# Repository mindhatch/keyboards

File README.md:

# keyboards!
<ul>
  <li>30-34 keys</li>
  <li>choc-spaced</li>
  <li>bluetooth-only</li>
  <li>1.5u thumb keys</li>
  <li>column staggered</li>
  <li>splayed ring and pinky columns</li>
  <li>mcu footprint fits spring-loaded pin headers</li>
</ul>

<h1>ルナ (luna)</h1>
<ul>
  <li>30 keys</li>
  <li>5&deg; splay on ring column</li>
  <li>12.5&deg; splay on pinky column</li>
  <li>switches can be soldered or used with hotswap sockets</li>
  <li>firmware can be found <a href="https://github.com/mindhatch/zmk-config-luna" alt="luna firmware">here</a></li>
</ul>
<br/><br/>

<br/><br/>

<h1>美奈子 (minako)</h1>
<ul>
  <li>32 keys</li>
  <li>5&deg; splay on ring column</li>
  <li>15&deg; splay on pinky column</li>
  <li>switches are solder-only</li>
  <li>firmware can be found <a href="https://github.com/mindhatch/zmk-config-minako" alt="minako firmware">here</a></li>
</ul>
<br/><br/>

<br/><br/>

<h1>アルテミス (artemis)</h1>
<ul>
  <li>34 keys</li>
  <li>5&deg; splay on ring column</li>
  <li>12.5&deg; splay on pinky column</li>
  <li>switches can be soldered or used with hotswap sockets</li>
  <li>firmware can be found <a href="https://github.com/mindhatch/zmk-config-artemis" alt="artemis firmware">here</a></li>
</ul>
<br/><br/>

<br/><br/>

<h1>ファントマ (la phantoma)</h1>
<ul>
  <li>30 keys</li>
  <li>5&deg; splay on ring column</li>
  <li>12.5&deg; splay on pinky column</li>
  <li>switches are solder-only</li>
  <li>directly inspired by and based on <a href="https://github.com/davidphilipbarr/36keys/tree/master/30keys/thephantom" alt="le phantom">le phantom</a> by <a href="https://github.com/davidphilipbarr/" alt="not your broom">broom</a></li>
  <li>firmware can be found <a href="https://github.com/mindhatch/zmk-config-phantoma" alt="artemis firmware">here</a></li>
</ul>
<br/><br/>

<br/><br/><br/><br/>

<sup>microcontroller footprint designed by <a href="https://github.com/jimmerricks/" alt="Jimmerricks">Jimmerricks</a> based on a design by <a href="https://github.com/50an6xy06r6n/" alt="50an6xy06r6n">50an6xy06r6n</a></sup><br/>
<sup>waterfall traces inspired by <a href="https://github.com/enzocoralc/" alt="enzocoralc">enzocoralc</a></sup>

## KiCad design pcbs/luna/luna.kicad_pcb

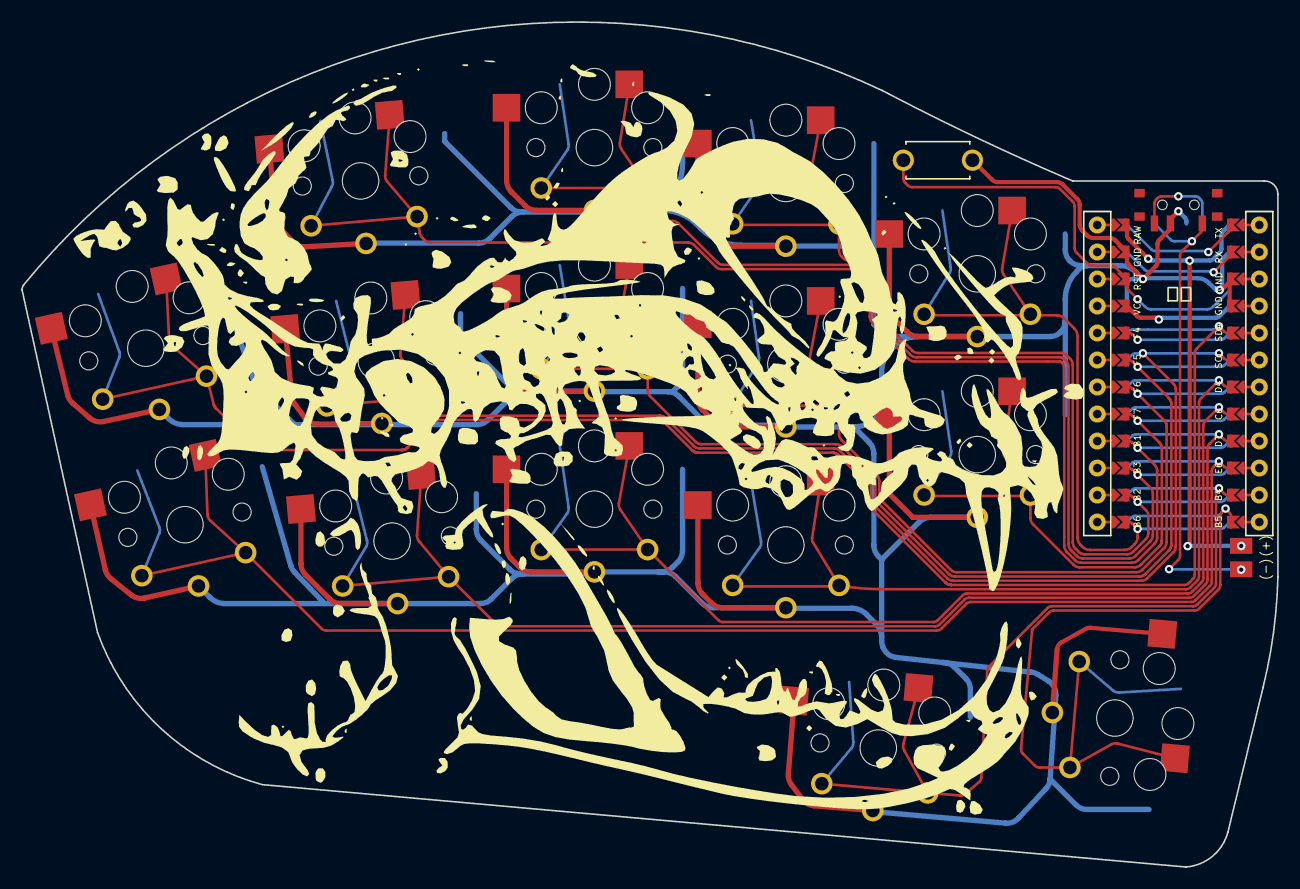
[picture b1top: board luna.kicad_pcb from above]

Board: 2 copper layers, 118.1 x 79.5 mm, 21 parts (1 on the bottom side), 19 nets.

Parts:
BT1: Battery_Cell; Battery_pads_reversible
PSW1: SW_SPDT; Power_reversible
SKULL: LOGO
SKULLback: LOGO
SW1, SW2, SW3, SW4, SW5, SW6, SW7, SW8, SW9, SW10, SW11, SW12, SW13: SW_PUSH; Kailh_socket_PG1350_optional_reversible_1u
SW14, SW15: SW_PUSH; Kailh_socket_PG1350_optional_reversible_15u
SW16: SW_Push; ResetSW
U1: ProMicro; ProMicro_jumpers

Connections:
GND: PSW1.2 (B), SW1.1, SW1.2, SW2.1, SW2.2, SW3.1, SW3.2, SW4.1, SW4.2, SW5.1, SW5.2, SW6.1, SW6.2, SW7.1, SW7.2, SW8.1, SW8.2, SW9.1, SW9.2, SW10.1, SW10.2, SW11.1, SW11.2, SW12.1, SW12.2, SW13.1, SW13.2, SW14.1, SW14.2, SW15.1, SW15.2, SW16.2, U1.3 (GND), U1.4 (GND), U1.23 (GND)
unnamed: BT1.2 (-), PSW1.1 (A)
raw: BT1.1 (+), U1.24 (RAW)
reset: SW16.1, U1.22 (RST)
switch1: SW1.1, SW1.2, U1.5 (SDA)
switch2: SW2.1, SW2.2, U1.16 (B1)
switch3: SW3.1, SW3.2, U1.15 (B3)
switch4: SW4.1, SW4.2, U1.14 (B2)
switch5: SW5.1, SW5.2, U1.13 (B6)
switch6: SW6.1, SW6.2, U1.10 (E6)
switch7: SW7.1, SW7.2, U1.6 (SCL)
switch8: SW8.1, SW8.2, U1.19 (F5)
switch9: SW9.1, SW9.2, U1.18 (F6)
switch10: SW10.1, SW10.2, U1.17 (F7)
switch11: SW11.1, SW11.2, U1.9 (D7)
switch12: SW12.1, SW12.2, U1.8 (C6)
switch13: SW13.1, SW13.2, U1.7 (D4)
switch14: SW14.1, SW14.2, U1.11 (B4)
switch15: SW15.1, SW15.2, U1.12 (B5)

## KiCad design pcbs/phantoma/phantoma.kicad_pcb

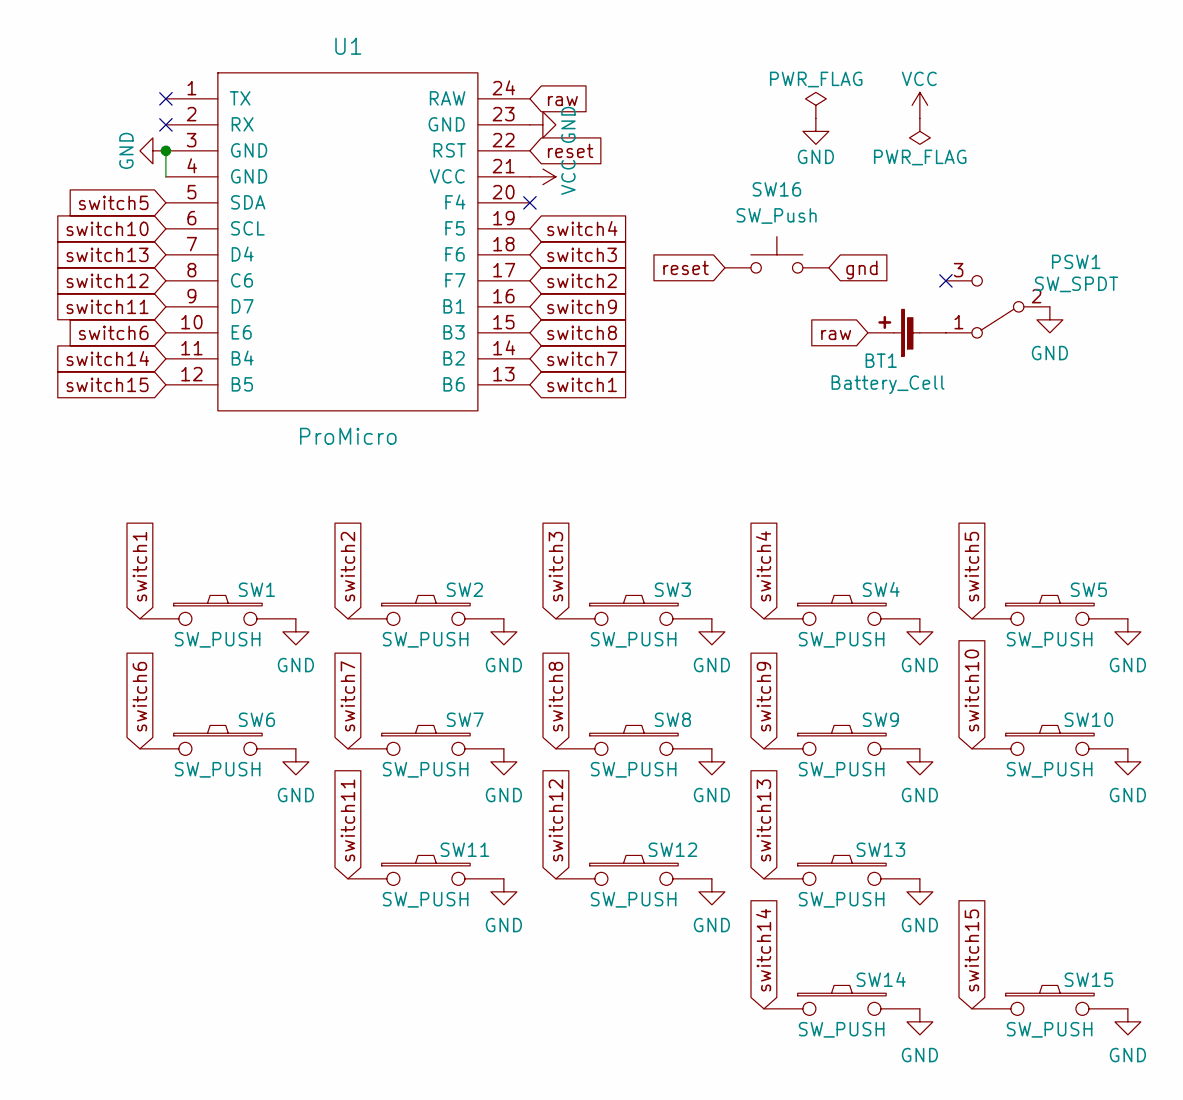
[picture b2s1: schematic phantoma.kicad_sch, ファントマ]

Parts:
BT1: Battery_Cell; Battery_pads_reversible
PSW1: SW_SPDT; Power_reversible
SW1, SW2, SW3, SW4, SW5, SW6, SW7, SW8, SW9, SW10, SW11, SW12, SW13, SW14, SW15: SW_PUSH; Choc_reversible
SW16: SW_Push; ResetSW
U1: ProMicro; ProMicro_jumpers

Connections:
GND: PSW1.2 (B), SW1.2, SW2.2, SW3.2, SW4.2, SW5.2, SW6.2, SW7.2, SW8.2, SW9.2, SW10.2, SW11.2, SW12.2, SW13.2, SW14.2, SW15.2, SW16.2, U1.3 (GND), U1.4 (GND), U1.23 (GND)
unnamed: BT1.2 (-), PSW1.1 (A)
VCC: U1.21 (VCC)
raw: BT1.1 (+), U1.24 (RAW)
reset: SW16.1, U1.22 (RST)
switch1: SW1.1, U1.13 (B6)
switch2: SW2.1, U1.17 (F7)
switch3: SW3.1, U1.18 (F6)
switch4: SW4.1, U1.19 (F5)
switch5: SW5.1, U1.5 (SDA)
switch6: SW6.1, U1.10 (E6)
switch7: SW7.1, U1.14 (B2)
switch8: SW8.1, U1.15 (B3)
switch9: SW9.1, U1.16 (B1)
switch10: SW10.1, U1.6 (SCL)
switch11: SW11.1, U1.9 (D7)
switch12: SW12.1, U1.8 (C6)
switch13: SW13.1, U1.7 (D4)
switch14: SW14.1, U1.11 (B4)
switch15: SW15.1, U1.12 (B5)

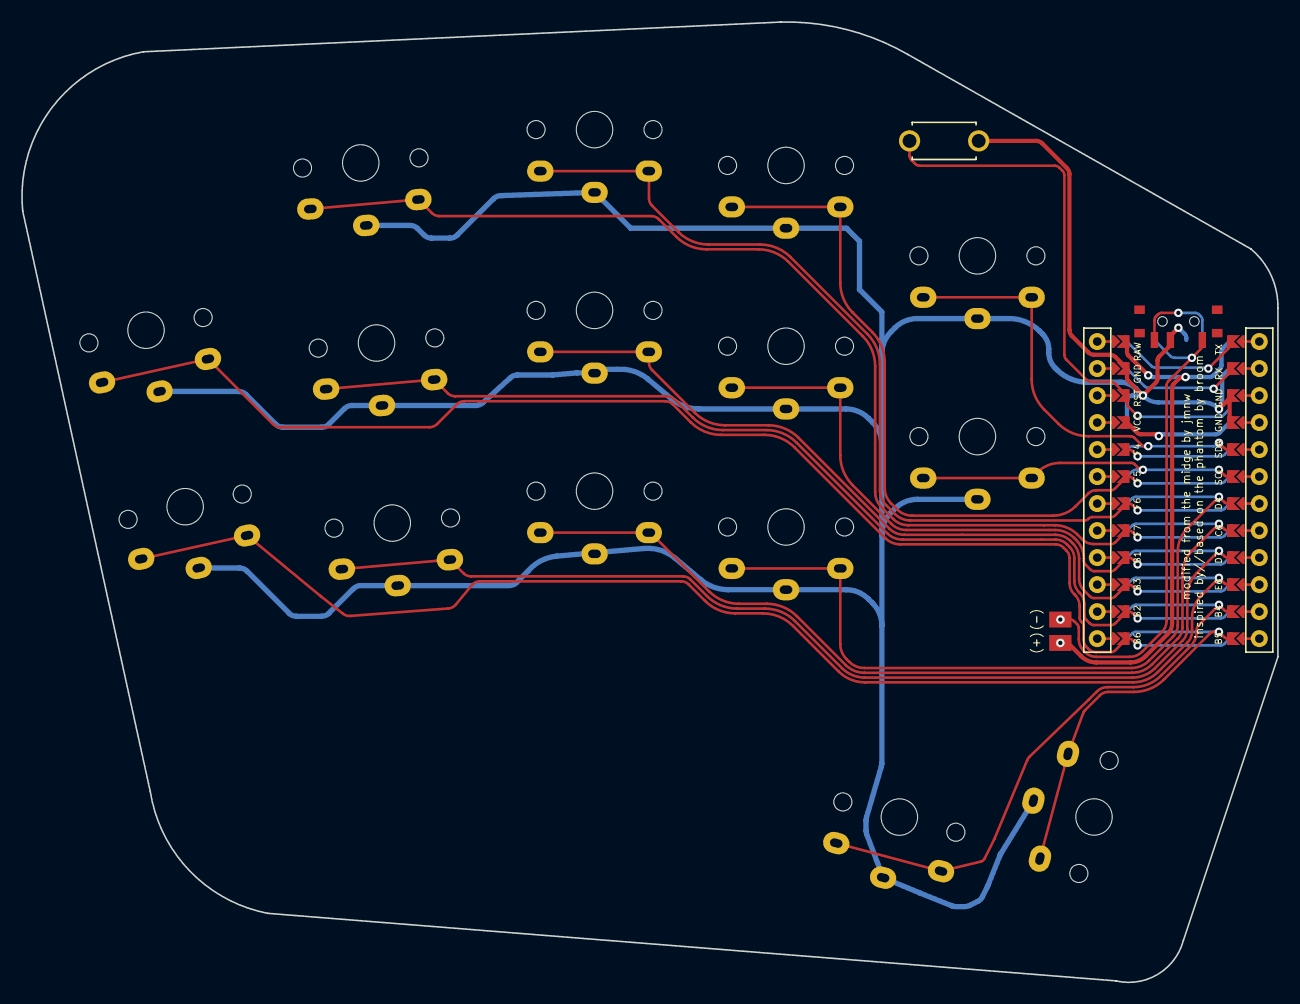
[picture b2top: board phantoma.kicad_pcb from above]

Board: 2 copper layers, 118.1 x 90.3 mm, 19 parts (0 on the bottom side), 19 nets.

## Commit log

2022-01-06 Create LICENSE
2022-01-06 cats rule everything around me
2022-01-06 thumb alignment
2022-01-06 alignment
2022-01-07 mounting holes
2022-01-07 fixed oopsie
2022-01-07 images
2022-01-07 housekeeping
2022-01-07 README
2022-01-08 oopsies
2022-01-08 add 32key
2022-01-09 lotsa changes
2022-01-09 add phantoma to README
2022-01-17 artemis firmware
2022-01-25 added reset footprint and generally outchea makin' changes
